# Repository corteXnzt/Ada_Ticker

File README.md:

# Ada_Ticker
PCB layout for a crypto ticker, water and medicine reminder and another time clock. Uses m5stamp pico with ST7789 OLED.

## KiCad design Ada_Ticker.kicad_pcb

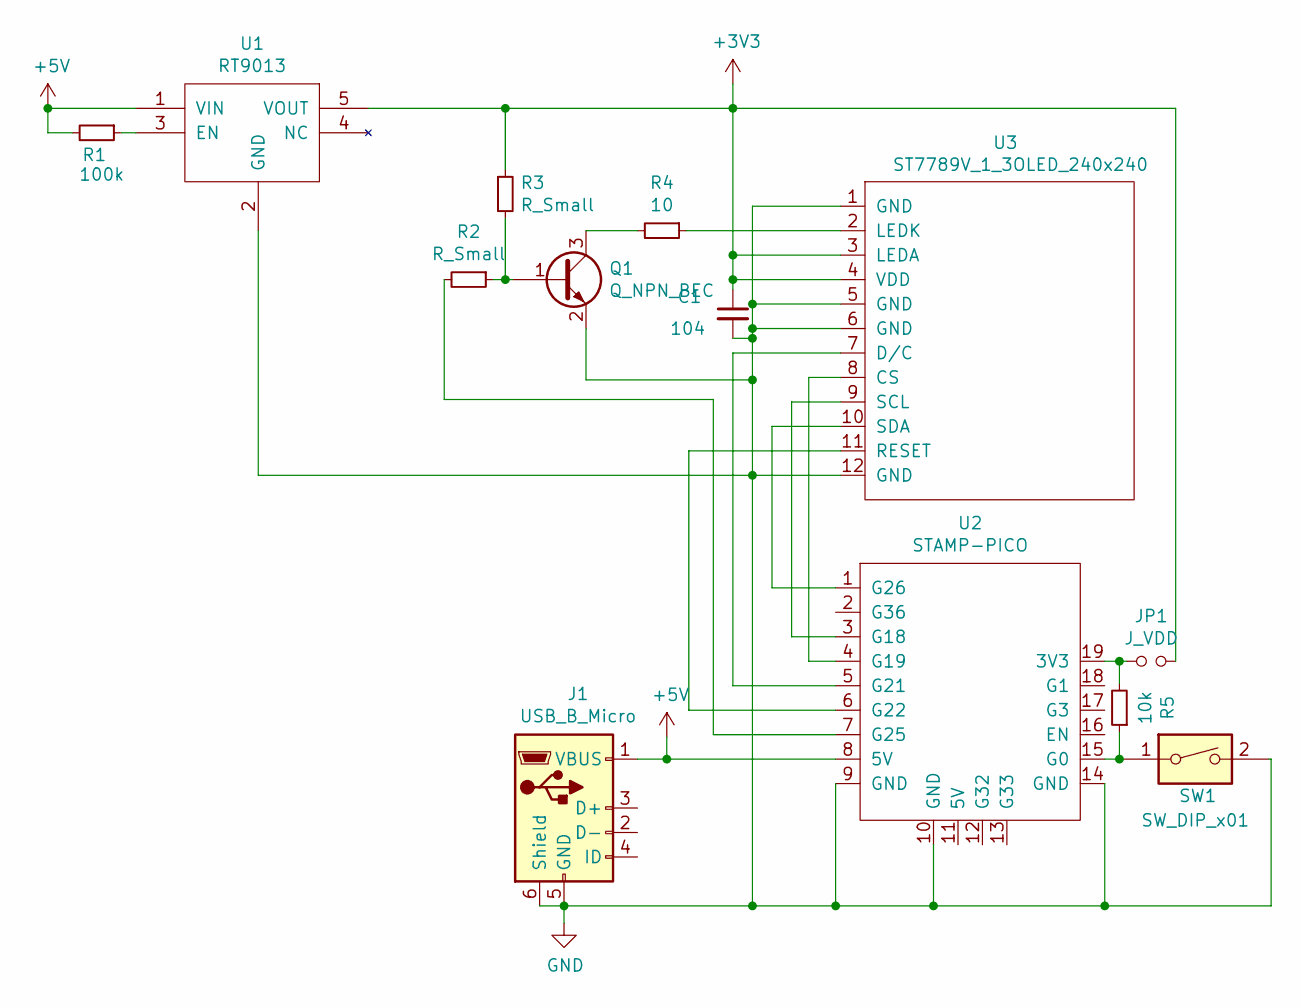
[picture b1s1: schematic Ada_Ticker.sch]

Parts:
C1: 104; C_0603_1608Metric_Pad1.08x0.95mm_HandSolder
J1: USB_B_Micro; micro_usb_4vlegs
JP1: J_VDD; SolderJumper-2_P1.3mm_Open_RoundedPad1.0x1.5mm
Q1: Q_NPN_BEC; SOT-23
R1: 100k; R_0603_1608Metric_Pad0.98x0.95mm_HandSolder
R2, R3: R_Small; R_0603_1608Metric_Pad0.98x0.95mm_HandSolder
R4: 10; R_0603_1608Metric_Pad0.98x0.95mm_HandSolder
R5: 10k; R_0603_1608Metric_Pad0.98x0.95mm_HandSolder
SW1: SW_DIP_x01; KMR221GLFS_BTN
U1: RT9013; SOT-23-5
U2: STAMP-PICO; M5STACK-STAMP-PICO
U3: ST7789V_1_3OLED_240x240; st7789_1_3OLED_240x240

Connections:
+3V3: C1.1, JP1.2, R3.1, U1.5 (VOUT), U3.3 (LEDA), U3.4 (VDD)
+5V: J1.1 (VBUS), R1.2, U1.1 (VIN), U2.8 (5V)
GND: C1.2, J1.5 (GND), J1.6 (Shield), Q1.2 (E), SW1.2, U1.2 (GND), U2.9 (GND), U2.10 (GND), U2.14 (GND), U3.1 (GND), U3.5 (GND), U3.6 (GND), U3.12 (GND)
unnamed: JP1.1, R5.2, U2.19 (3V3)
unnamed: Q1.1 (B), R2.1, R3.2
unnamed: Q1.3 (C), R4.2
unnamed: R1.1, U1.3 (EN)
unnamed: R2.2, U2.7 (G25)
unnamed: R4.1, U3.2 (LEDK)
unnamed: R5.1, SW1.1, U2.15 (G0)
unnamed: U2.1 (G26), U3.10 (SDA)
unnamed: U2.3 (G18), U3.9 (SCL)
unnamed: U2.4 (G19), U3.8 (CS)
unnamed: U2.5 (G21), U3.7 (D/C)
unnamed: U2.6 (G22), U3.11 (RESET)

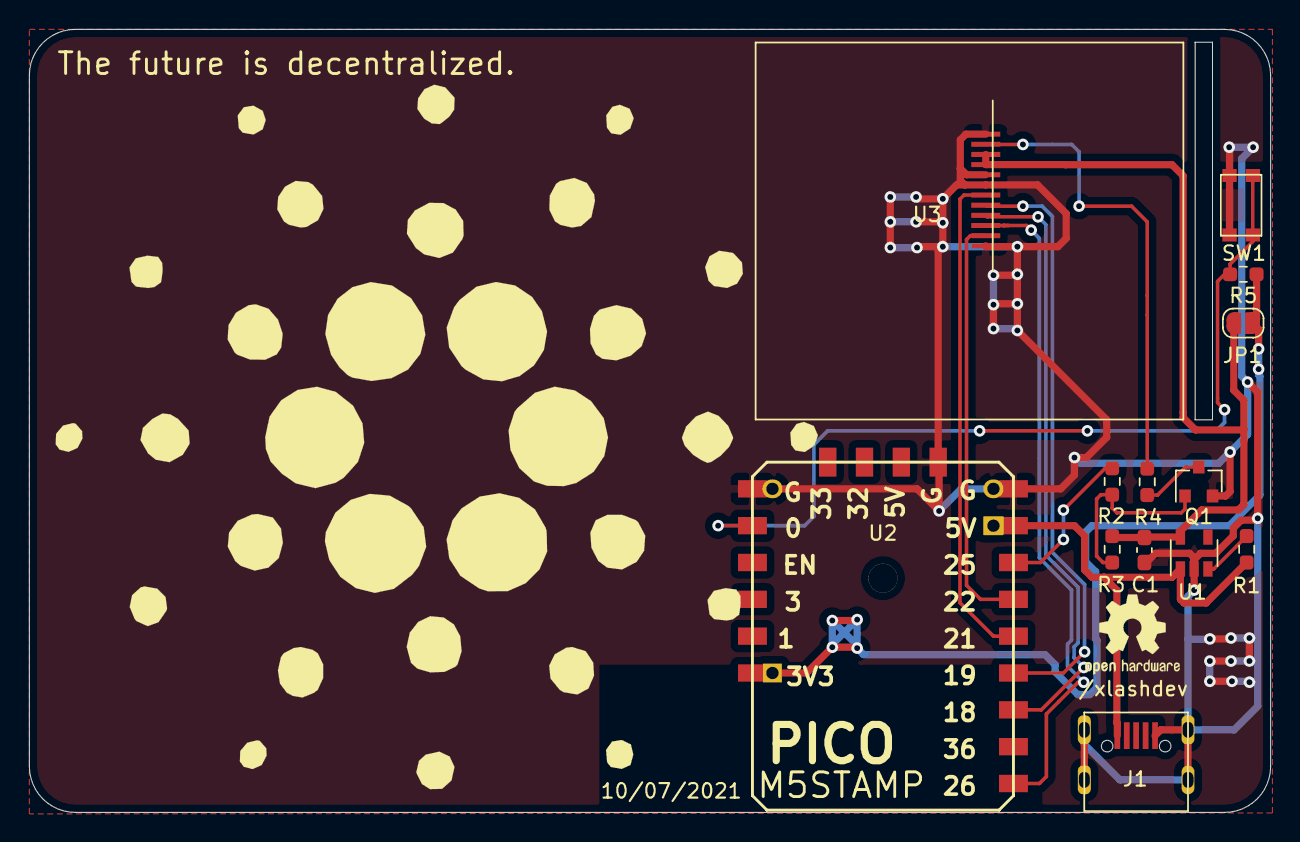
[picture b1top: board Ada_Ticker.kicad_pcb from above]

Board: 2 copper layers, 85.6 x 54.0 mm, 13 parts (0 on the bottom side), 15 nets.
